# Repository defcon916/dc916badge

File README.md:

# dc916badge

Source files for DC916 badge.  KiCAD project, plus dependencies/imported libraries.

If you have trouble importing into KiCAD, try importing dc916

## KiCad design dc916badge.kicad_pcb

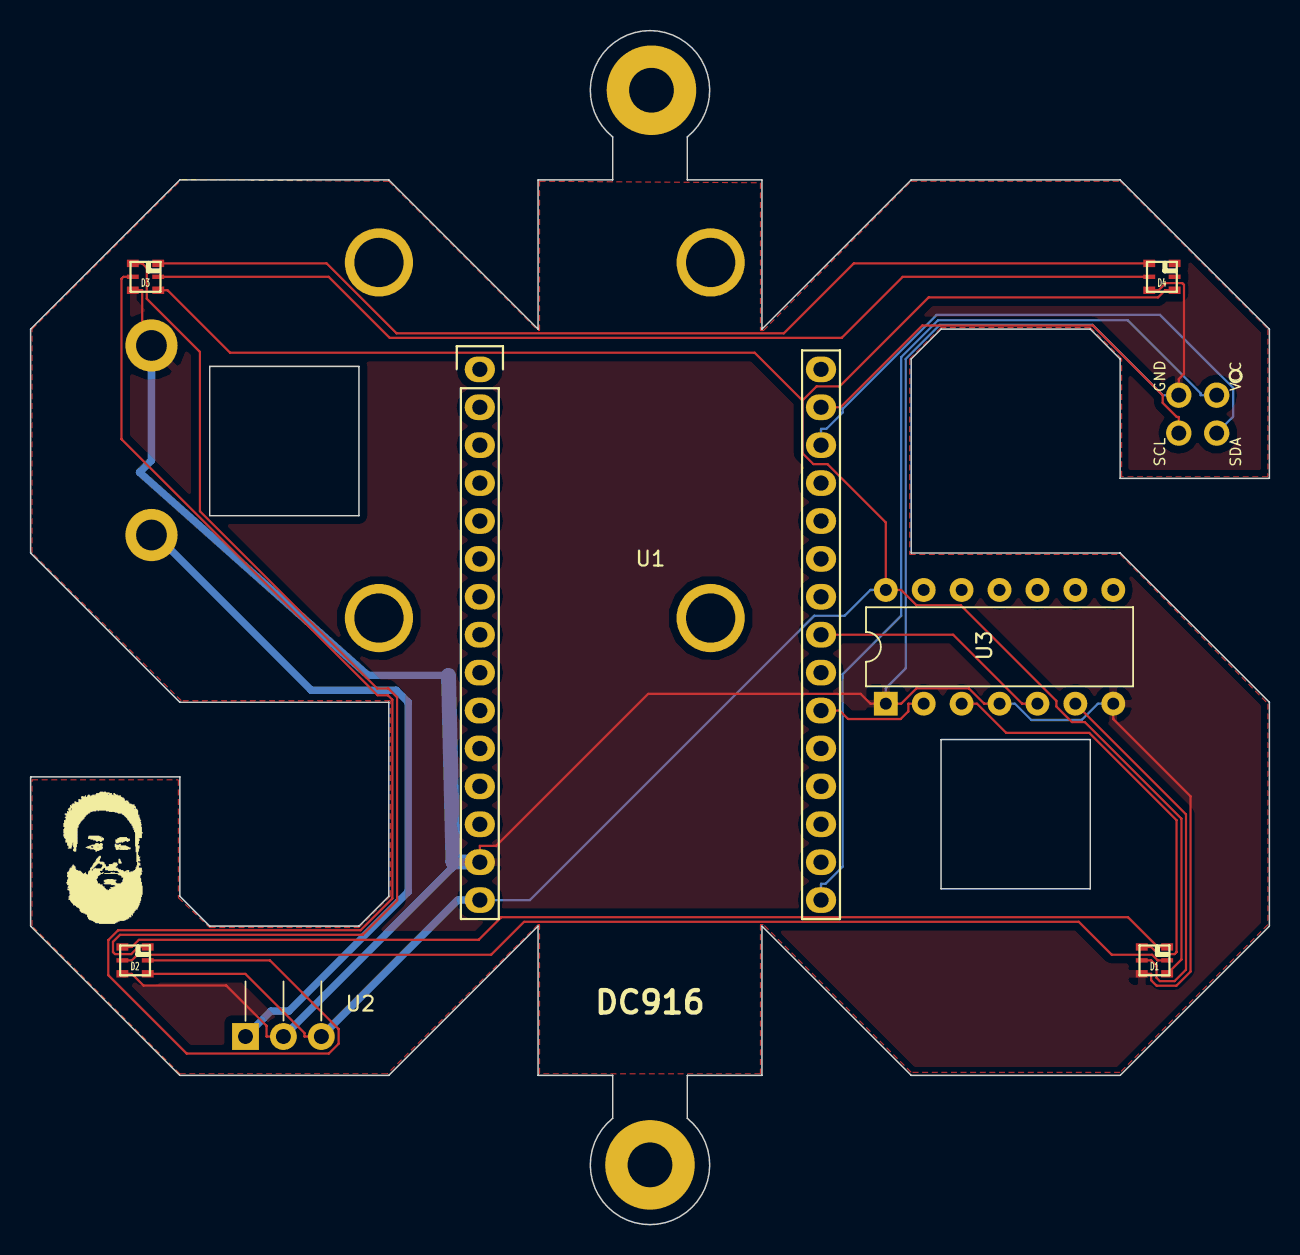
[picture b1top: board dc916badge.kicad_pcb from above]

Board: 2 copper layers, 83.0 x 80.0 mm, 10 parts (1 on the bottom side), 16 nets.

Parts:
BT1: 9v; BatteryHolder_9Volt_Keystone_1294
D1, D2, D3, D4: APA102; APA102-2020
U1: nodemcu; NodeMCU_Amica_R2
U2: LM7805_TO220; TO-220-3_Horizontal
U3: 74AHC125; DIP-14_W7.62mm
X1: shit; Badgelife-Shitty-2x2
nilesface: nilesface_smaller

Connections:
3v3VDC: U1.16, X1.1
5VDC: D1.5, D2.5, D3.5, D4.5, U1.15, U2.3, U3.14
9VDC: BT1.1, U2.1
CLK: U1.23, U3.5
CLK5: D1.2, U3.3
GND: BT1.2, D1.4, D2.4, D3.4, D4.4, U1.14, U2.2, U3.1, U3.4, U3.7, X1.2
MOSI: U1.21, U3.2
MOSI5: D1.3, U3.6
unnamed: D1.1, D2.2
unnamed: D1.6, D2.3
unnamed: D2.1, D3.2
unnamed: D2.6, D3.3
unnamed: D3.1, D4.2
unnamed: D3.6, D4.3
SCL: U1.29, X1.3
SDA: U1.28, X1.4

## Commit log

2018-07-15 replicating from bitbucket
2018-07-15 added archive version of project
2018-07-15 Created Readme
2018-07-29 Create dc916_test0_partymode.ino
    party mode badge test, is r
